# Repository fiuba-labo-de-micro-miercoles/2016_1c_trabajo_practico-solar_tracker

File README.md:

# Solar Tracker

Para configurar el oscilador externo a 8MHz:

  avrdude -c usbtiny -p m88 -U lfuse:r:-:i -F		
  avrdude -c usbtiny -p m88 -U lfuse:w:0xE2:m -F

# ¡GRACIAS A LOS QUE HICIERON POSIBLE ESTE PROYECTO!

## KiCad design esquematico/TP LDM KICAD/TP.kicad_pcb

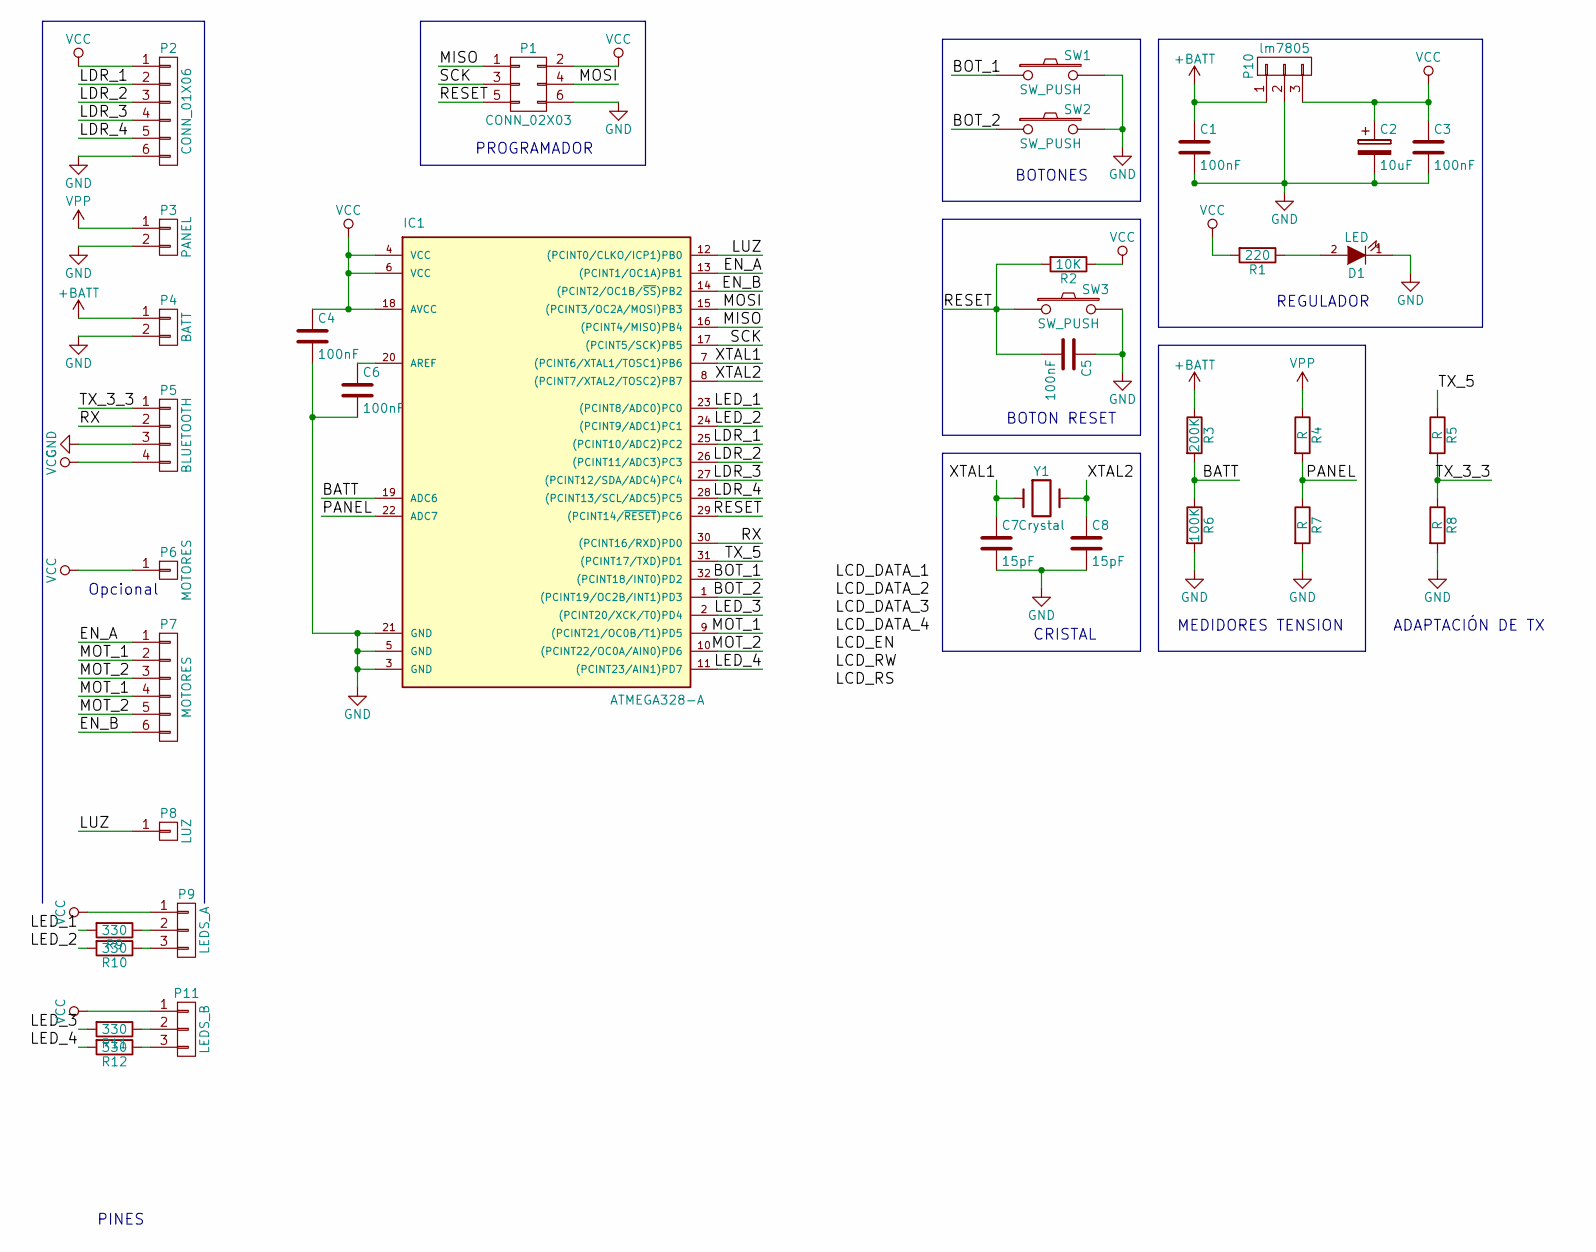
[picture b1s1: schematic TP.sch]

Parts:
C1, C3, C4, C5, C6: 100nF; C_Radial_D5_L6_P2.5
C2: 10uF; C_Radial_D5_L6_P2.5
C7, C8: 15pF; C_Radial_D5_L6_P2.5
D1: LED; LED-5MM
IC1: ATMEGA328-A; ATMEGA328PARALCI
P1: CONN_02X03; Pin_Header_Straight_2x03
P2: CONN_01X06; Pin_Header_Straight_1x06
P3: PANEL; Pin_Header_Straight_1x02
P4: BATT; Pin_Header_Straight_1x02
P5: BLUETOOTH; Pin_Header_Straight_1x04
P6: MOTORES; Pin_Header_Straight_1x01
P7: MOTORES; Pin_Header_Straight_1x06
P8: LUZ; Pin_Header_Straight_1x01
P9: LEDS_A; Pin_Header_Straight_1x03
P10: lm7805; Pin_Header_Straight_1x03
P11: LEDS_B; Pin_Header_Straight_1x03
R1: 220; Resistor_Horizontal_RM7mm
R2: 10K; Resistor_Horizontal_RM7mm
R3: 200K; Resistor_Horizontal_RM7mm
R4, R5, R7, R8: R; Resistor_Horizontal_RM7mm
R6: 100K; Resistor_Horizontal_RM7mm
R9, R10, R11, R12: 330; Resistor_Horizontal_RM7mm
SW1, SW2, SW3: SW_PUSH; SW_PUSH_SMALL
Y1: Crystal; Crystal_HC50-U_Vertical

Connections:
+BATT: C1.1, P4.1, P10.1, R3.1
/BATT: IC1.19 (ADC6), R3.2, R6.1
/BOT_1: IC1.32 ((PCINT18/INT0)PD2), SW1.1
/BOT_2: IC1.1 ((PCINT19/OC2B/INT1)PD3), SW2.1
/EN_A: IC1.13 ((PCINT1/OC1A)PB1), P7.1
/EN_B: IC1.14 ((PCINT2/OC1B/~SS~)PB2), P7.6
/LDR_1: IC1.25 ((PCINT10/ADC2)PC2), P2.2
/LDR_2: IC1.26 ((PCINT11/ADC3)PC3), P2.3
/LDR_3: IC1.27 ((PCINT12/SDA/ADC4)PC4), P2.4
/LDR_4: IC1.28 ((PCINT13/SCL/ADC5)PC5), P2.5
/LED_1: IC1.23 ((PCINT8/ADC0)PC0), R9.2
/LED_2: IC1.24 ((PCINT9/ADC1)PC1), R10.2
/LED_3: IC1.2 ((PCINT20/XCK/T0)PD4), R11.2
/LED_4: IC1.11 ((PCINT23/AIN1)PD7), R12.2
/LUZ: IC1.12 ((PCINT0/CLKO/ICP1)PB0), P8.1
/MISO: IC1.16 ((PCINT4/MISO)PB4), P1.1
/MOSI: IC1.15 ((PCINT3/OC2A/MOSI)PB3), P1.4
/MOT_1: IC1.9 ((PCINT21/OC0B/T1)PD5), P7.2, P7.4
/MOT_2: IC1.10 ((PCINT22/OC0A/AIN0)PD6), P7.3, P7.5
/PANEL: IC1.22 (ADC7), R4.2, R7.1
/RESET: C5.2, IC1.29 ((PCINT14/~RESET~)PC6), P1.5, R2.2, SW3.1
/RX: IC1.30 ((PCINT16/RXD)PD0), P5.2
/SCK: IC1.17 ((PCINT5/SCK)PB5), P1.3
/TX_3_3: P5.1, R5.2, R8.1
/TX_5: IC1.31 ((PCINT17/TXD)PD1), R5.1
/XTAL1: C7.1, IC1.7 ((PCINT6/XTAL1/TOSC1)PB6), Y1.1
/XTAL2: C8.1, IC1.8 ((PCINT7/XTAL2/TOSC2)PB7), Y1.2
GND: C1.2, C2.2, C3.2, C4.2, C5.1, C6.2, C7.2, C8.2, D1.1 (K), IC1.3 (GND), IC1.5 (GND), IC1.21 (GND), P1.6, P2.6, P3.2, P4.2, P5.3, P10.2, R6.2, R7.2, R8.2, SW1.2, SW2.2, SW3.2
unnamed: C6.1, IC1.20 (AREF)
unnamed: D1.2 (A), R1.1
unnamed: P9.2, R9.1
unnamed: P9.3, R10.1
unnamed: P11.2, R11.1
unnamed: P11.3, R12.1
VCC: C2.1, C3.1, C4.1, IC1.4 (VCC), IC1.6 (VCC), IC1.18 (AVCC), P1.2, P2.1, P5.4, P6.1, P9.1, P10.3, P11.1, R1.2, R2.1
VPP: P3.1, R4.1

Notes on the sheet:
Opcional
BOTONES
BOTON RESET
CRISTAL
PINES
REGULADOR
MEDIDORES TENSION
PROGRAMADOR
ADAPTACIÓN DE TX

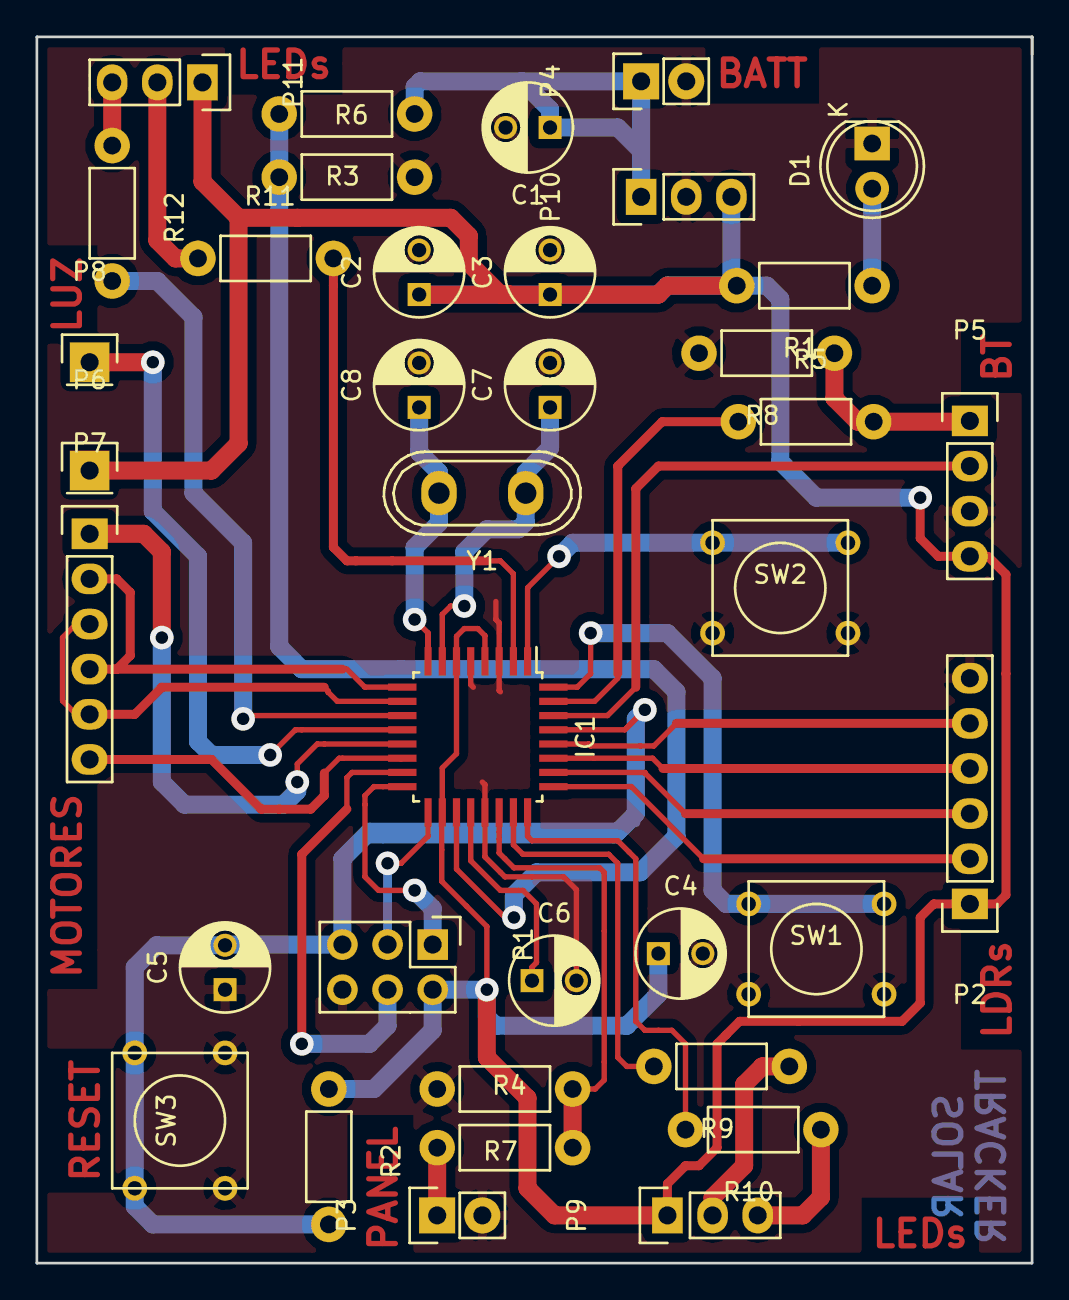
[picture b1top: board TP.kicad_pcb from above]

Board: 2 copper layers, 56.0 x 69.0 mm, 37 parts (0 on the bottom side), 36 nets.

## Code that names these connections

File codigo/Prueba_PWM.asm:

;*****************************************************
;* 	Programa PWM
;*
;*  Created: 27/05/2016
;*  Autor: Joaquín Ulloa
;*	
;*	f_outPWM = f_clkIO / (prescaler * 256)
;*	Configuracion Fast Pwm
;*	
;***************************************************** 

.include "m88pdef.inc"   	;Incluye los nombres de los registros del micro
.include "avr_macros.inc"	;Incluye los macros
.listmac					;Permite que se expandan las macros en el listado
;***************************************************** 
.DSEG						;Se abre un segmento de datos para definir variables
.DEF	PWM_DATA 	= R16
.EQU	PWM_DC	= 128		;Duty cicle {0,255}
.CSEG
;***************************************************** 
.ORG 0x0000					;se setean los registros de interrupciones
RJMP MAIN_PWM


MAIN_PWM:
;Se inicializa el stack pointer
	LDI PWM_DATA,LOW(RAMEND)
	OUT SPL,PWM_DATA
	LDI	PWM_DATA,HIGH(RAMEND)
	OUT SPH,PWM_DATA
;Se inicializan como salida los pines de PWM
	output PWM_DATA,DDRB
	SBI DDRB,1				;(PCINT1/OC1A) PB1
	SBI DDRB,2				;(PCINT2/OC1B/SS) PB2
	input DDRB,PWM_DATA
	output PWM_DATA,DDRB
	SBI DDRD,5				;(PCINT21/OC0B/T1) PD5
	SBI DDRD,6				;(PCINT22/OC0A/AIN0) PD6
	input DDRB,PWM_DATA

;Se inicializan como Fast PWM y non-inverting mode
	;Fast PWM: WGM02=0 (por defecto), WGM01=1 y WGM00=1
	;Non-inverting mode: COM0A1=1 y COM0A0=0
	;Descripcion de registros en seccion 15.9 (pag 106-112)
	LDI PWM_DATA,PWM_DC		;Se define el duty cycle
	output OCR0A,PWM_DATA	;Se carga el duty cycle
	input PWM_DATA,TCCR0A	;Timer/counter control register A
	ANDI PWM_DATA,(~0xF3)	;Mascara para no tocar bits 2 y 3
	ORI PWM_DATA,((1<<WGM01)|(1<<WGM00)|(1<<COM0A1)|(0<<COM0A0)|(1<<COM0B1)|(0<<COM0B0))	;fast PWM, non-inverting
	output TCCR0A,PWM_DATA
;Se inicializa el prescaler del PWM
	input PWM_DATA,TCCR0A	;Timer/counter control register B
	;hacer mascara de forma tal que los bits 0, 1, 2 queden en 0
	ANDI PWM_DATA,(~0x07)	;Mascara para no tocar bits 3 a 7
	ORI PWM_DATA,((0<<CS00)|(1<<CS01)|(0<<CS02))	;Prescaler = 8
	output TCCR0B,PWM_DATA

	;hasta aca se configuro el pwm para el timer de 8 bits, falta el de 16m

LOOP:
	RJMP LOOP

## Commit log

2016-05-11 Add files via upload
    Se sube el anteproyecto.
2016-05-11 Add files via upload
    Se suben los diagramas de flujo y bloques
2016-05-11 Add files via upload
    Se sube la convención de uso de registros preliminar.
2016-05-11 Add files via upload
    Se sube la hoja de datos de la familia del micro a usar
2016-05-13 Ahí subí el proyecto en kicad. SEGURO tira error en el ATMEGA328PARALCI.kicad_mod cuando vayas a seguir ruteando Joaco.
2016-05-13 V 1.0 terminada PCB micro + archivos fabricacion LCI
2016-05-13 agrego RAR con archivos de fabricacion
2016-05-13 Ya tenemos puerto serie para el atmega88pa
2016-05-19 prueba con el bluetooth [esta mal el nombre]
2016-05-26 AHI SUBO EL ESQUEMATICO EN PDF
2016-05-26 TX Y RX DEL MODULO BLUETOOTH ANDANDO!
2016-05-26 Prueba del ADC.. para variar no anda tdv jaja
2016-05-27 Codigo PWM. A las dos salidas de 8bit solo les falta una mascara y estan. Las de 16bit no estan configuradas todavia.
2016-05-27 aca subo andando el ADC
2016-05-27 PARA RECORDAR COMO USAR BASICO GIT
2016-05-27 No esta testeado
    Falta el PWM de 16bits, se hara cuando ande el de 8bits
2016-05-27 agrego avr_macros
2016-05-27 ahi subo el pwm de joaco andando
2016-05-29 Agrego hojas de datos de micro, controlador de carga de panel solar y algunas especificaciones de motores
2016-05-29 Revert "Agrego hojas de datos de micro, controlador de carga de panel solar y algunas especificaciones de motores"
    This reverts commit 7b0eeaa5e9d731c8c791ec66e3d50fa0e535bb60.
2016-05-29 Es un seudo codigo pedorro, basica mente lo mismo que el diagram de bloques. Pero sirvio para darme cuenta que nos falta aprender como hacer una interrupcion serie e ir y salir de modo bajo consumo.
2016-05-29 Agrego el codijo de pwm del puerto b supuestamente terminada y paso todo el codigo de prueba a la carpeta prueba
2016-05-29 borro el leeme
2016-05-29 erregle una cagada que me habia mandado con pwm_b
2016-05-29 Agrego codigo para PWM puerto D, 16bits, pero usado como de 8
2016-05-30 arreglo de mascaras, funciones set y reset
2016-05-30 idem anterior. HAY QUE PONER TODO EN UNO
2016-05-30 COMENTARIOS. LEERgit add codigo/Solar_Tracker.asm
2016-05-30 me molesta que esté!
2016-05-30 Segmento de codigo de las rutinas de delay. HANDICAP
2016-05-30 DEJO COMENTARIOS EN EL README.MD
2016-05-30 basico. falta terminar. idea del modulo ADC
2016-05-30 basico. falta terminar. idea del modulo pwm
2016-05-30 arreglo de errores en pwm_d y modificar el main de solar tracker
2016-05-30 agrego la funcion para seleccionar la entrada
2016-05-30 empece con el puerto serie. HAY QUE HACERLO POR INTERRUPCION
2016-05-30 cambios minimos
2016-06-01 ahi anda por interrupcion
2016-06-01 archivo con funciones de la luz
2016-06-01 archivo con las frases para transmitir
2016-06-01 definicion de constantes y registros de todo el proyecto
2016-06-01 pase las directivas de preprocesador al header general del proyecto
2016-06-01 OJO! HABIA UN R16 HARDCODEADO Y CAMBIE t0 a AUX
2016-06-02 LO QUE HICIMOS EN CLASE
2016-06-02 cambios que me acorde antes de dormir. chequear mañana mas lucido
2016-06-03 cambios generales.
2016-06-03 cambios menores.
2016-06-05 empece a hacer la lectura de ldrs gracias a agus
2016-06-06 cambios con agus al lado en biblioteca
2016-06-06 para futura implementacion con LCD
2016-06-06 cambios hechos en el labi
2016-06-08 Aplique los cambios que dijo Ricardo Arias sobre el buffer
2016-06-08 codigo de Agus. Las ideas ya las puse en LDRS.inc
2016-06-08 version con todos los PWM necesarios
2016-06-08 ya estan listos los pwm y las macros para set y reset
2016-06-08 empezando a hacer lo de mover motores
2016-06-08 habia un error en ldrs_mean
2016-06-09 PROYECTO COMPILANDO. HAY QUE DEBUGUEAR
2016-06-09 habia unos errores en procedimientos
2016-06-13 cambie en el esquematico la luz, siguen faltando funciones de conversion, cambios generales. Tp VIRTUALMENTE funcionando
2016-06-17 hice un proyecto aparte para pruebas antes de ir al definitivo
2016-06-17 ahi agregue la funcion de pycard de convertir del adc al dato a transmitir
2016-06-18 andando adc (ldrs,bateria y panel), puerto serie y el resto probar
2016-06-18 andando bateria, panel solar, logica luz y el sleep en el main. faltan motores, calibrar motores, y calibrar panel y ldrs
2016-06-18 despues que se fueron joaco y agus. manda la tension por bt. supongo que todo lo anterior sigue andando
2016-06-19 ANDAN LOS MOTORES, FALTA ORIENTAR EL PANEL EN FUNCION DE LDRS (QUE ANDAN ESTOS ULTIMOS) Y FALTA AGREGAR BT Y CHEQUEAR QUE ANDE BIEN EL SLEEP
2016-06-19 EL PANEL SE ORIENTA EN AZIMUTgit add . HAY QUE MEJORAR, TARDA 8 MUESTRAS EN RECONOCER
2016-06-19 AHORA SI ANDAN BIEN LOS MOTORES! CONFIGURABAMOS MAL TCCR1A EN PWM git add .git add .
2016-06-19 se agregaron smooth_move y smooth_brake para que no cabecee y ORIENTATE_SOLAR_PANEL anda en el eje azimutal y no se mueve en maxima luz. FALTA elevacion.
2016-06-19 ANDA EL SLEEP_MODE CON TIMER, EN CONJUNTO CON EL PROYECTO. CHEQUEAR QUE HACE ALGO RARO CON LA TRANSMISION DE DATOS POR BT
2016-06-20 cuando sale de VBATERRY_TO_ASCII vuelva a cualquier lado. hace lio con PC, pero convierte bien
2016-06-20 anda todo, excepto un bug en la lectura de la tension del panel. falta probar la luz y hacer lindo la comunicacion bluetooth.
2016-06-21 chequear la calibracion, cuando se va a dormir y la luz
2016-06-22 ajustes despues de que anduvo bien. La luz se ajusta segun la carga de la bateria, el panel esta ajustado para luz de interior. no probe las comparaciones de ldrs. POR PROBLEMAS EN LOS LDRS, volver a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
2016-06-22 En la funcion ORIENTATE_SOLAR_PANEL tome el promedio para comparar.
2016-06-29 subo el informe en pdf
